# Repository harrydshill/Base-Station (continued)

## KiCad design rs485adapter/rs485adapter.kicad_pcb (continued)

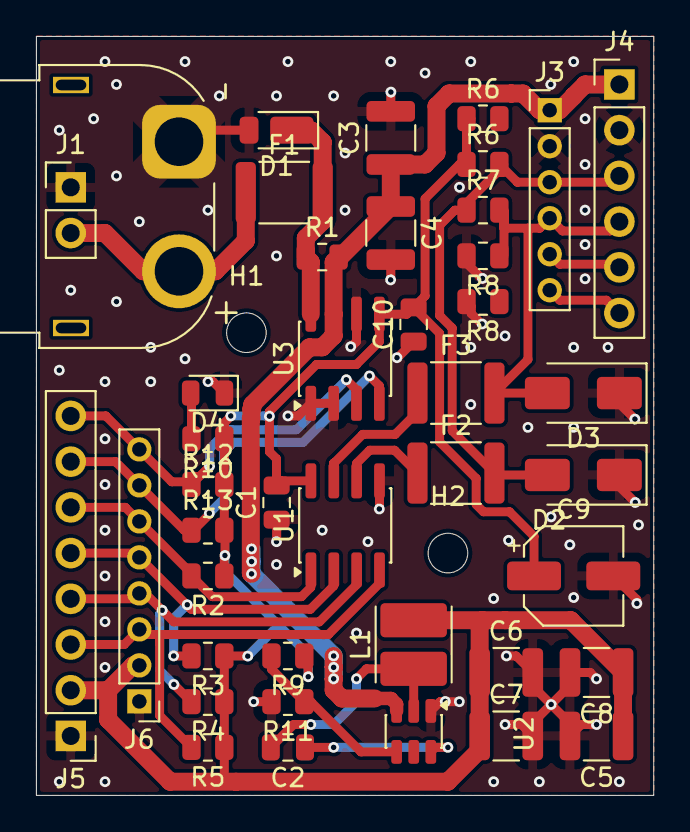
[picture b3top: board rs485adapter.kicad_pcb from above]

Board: 2 copper layers, 34.3 x 42.2 mm, 44 parts (0 on the bottom side), 21 nets.

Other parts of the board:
R6#2, R8#2: 10k; R_0805_2012Metric

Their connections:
+5V: R6#2.1; also elsewhere on the board
GND: R8#2.2; also elsewhere on the board

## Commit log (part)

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2026-04-29 minor
2026-04-29 schema
2026-04-29 bleugh
2026-04-30 pushes
